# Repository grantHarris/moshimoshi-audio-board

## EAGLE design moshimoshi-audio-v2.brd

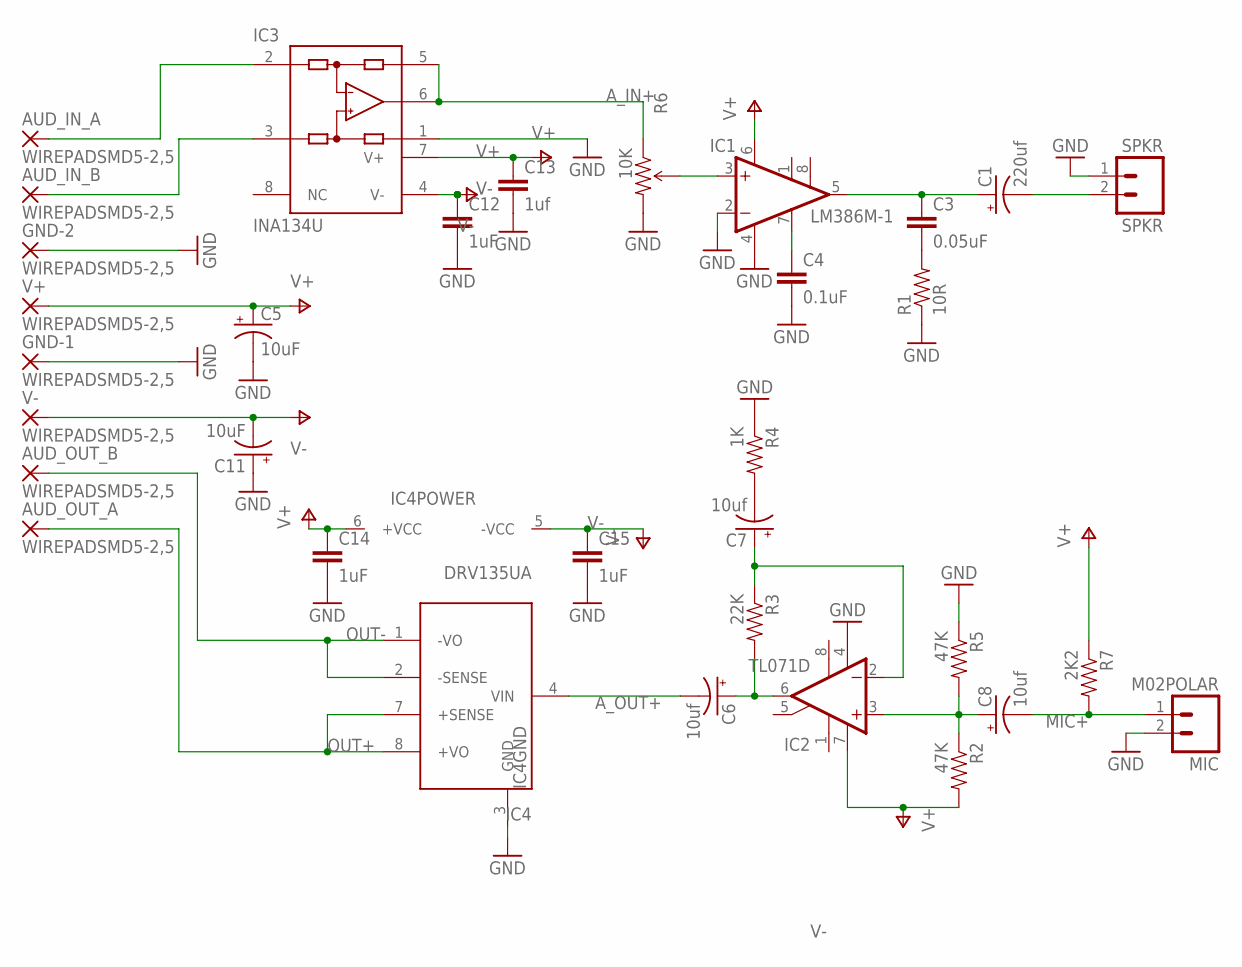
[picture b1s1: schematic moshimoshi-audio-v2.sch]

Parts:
AUD_IN_A: WIREPADSMD5-2,5; 5-2,5
AUD_IN_B: WIREPADSMD5-2,5; 5-2,5
AUD_OUT_A: WIREPADSMD5-2,5; 5-2,5
AUD_OUT_B: WIREPADSMD5-2,5; 5-2,5
C1: 220uf; CPOL-RADIAL-100UF-25V
C3: 0.05uF; 0805
C4: 0.1uF; 0603-CAP
C5, C11: 10uF; EIA3216
C6, C7, C8: 10uf; CPOL-RADIAL-10UF-25V
C12, C14, C15: 1uF; 0805
C13: 1uf; 0805
GND-1, GND-2: WIREPADSMD5-2,5; 5-2,5
IC1: LM386M-1; SO08
IC2: TL071D; SO08
IC3: INA134U; SO08
IC4: DRV135UA; SO08
MIC: M02POLAR; MOLEX-1X2
R1: 10R; 0805
R2, R5: 47K; 0603-RES
R3: 22K; 0603-RES
R4: 1K; 0603-RES
R6: 10K; TRIMPOT-3MM-2
R7: 2K2; 0603-RES
SPKR: SPKR; MOLEX-1X2
V+: WIREPADSMD5-2,5; 5-2,5
V-: WIREPADSMD5-2,5; 5-2,5

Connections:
A_IN+: IC3.5 (SENSE), IC3.6 (OUT), R6.1 (CCW)
A_OUT+: C6.2 (-), IC4.4 (VIN)
GND: C4.2, C5.C (-), C11.A (+), C12.2, C13.2, C14.2, C15.2, GND-1.1, GND-2.1, IC1.2 (-IN), IC1.4 (GND), IC2.4 (V-), IC3.1 (REF), IC4.3 (GND), MIC.2, R1.1, R4.1, R5.1, R6.3 (CW), SPKR.1
IN+: AUD_IN_B.1, IC3.3 (+IN)
IN-: AUD_IN_A.1, IC3.2 (-IN)
MIC+: C8.2 (-), MIC.1, R7.2
unnamed: C1.2 (-), SPKR.2
unnamed: IC1.3 (+IN), R6.2 (WIPER)
unnamed: C1.1 (+), C3.1, IC1.5 (OUT)
unnamed: C4.1, IC1.7 (BYPASS)
unnamed: C3.2, R1.2
unnamed: C6.1 (+), IC2.6 (OUT), R3.2
unnamed: C7.1 (+), IC2.2 (-IN), R3.1
unnamed: C7.2 (-), R4.2
unnamed: C8.1 (+), IC2.3 (+IN), R2.1, R5.2
OUT+: AUD_OUT_A.1, IC4.7 (+SENSE), IC4.8 (+VO)
OUT-: AUD_OUT_B.1, IC4.1 (-VO), IC4.2 (-SENSE)
V+: C5.A (+), C13.1, C14.1, IC1.6 (VS), IC2.7 (V+), IC3.7 (V+), IC4.6 (+VCC), R2.2, R7.1, V+.1
V-: C11.C (-), C12.1, C15.1, IC3.4 (V-), IC4.5 (-VCC), V-.1

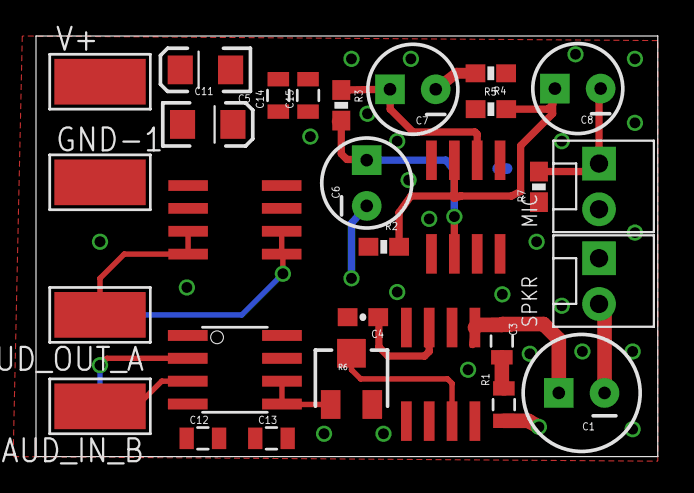
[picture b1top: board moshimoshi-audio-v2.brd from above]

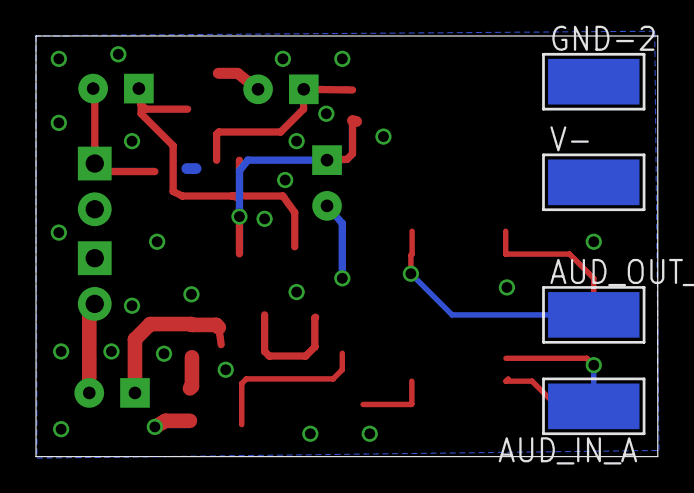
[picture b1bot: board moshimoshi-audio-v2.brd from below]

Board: 2 copper layers, 34.5 x 23.4 mm, 33 parts (4 on the bottom side), 19 nets.

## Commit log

2016-05-18 Moshi moshi pcb and board files
2016-07-07 Updated version with OW changes

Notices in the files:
parts and their libraries:
SparkFun-Capacitors: Licensing: Creative Commons ShareAlike 4.0 International - https://creativecommons.org/licenses/by-sa/4.0
